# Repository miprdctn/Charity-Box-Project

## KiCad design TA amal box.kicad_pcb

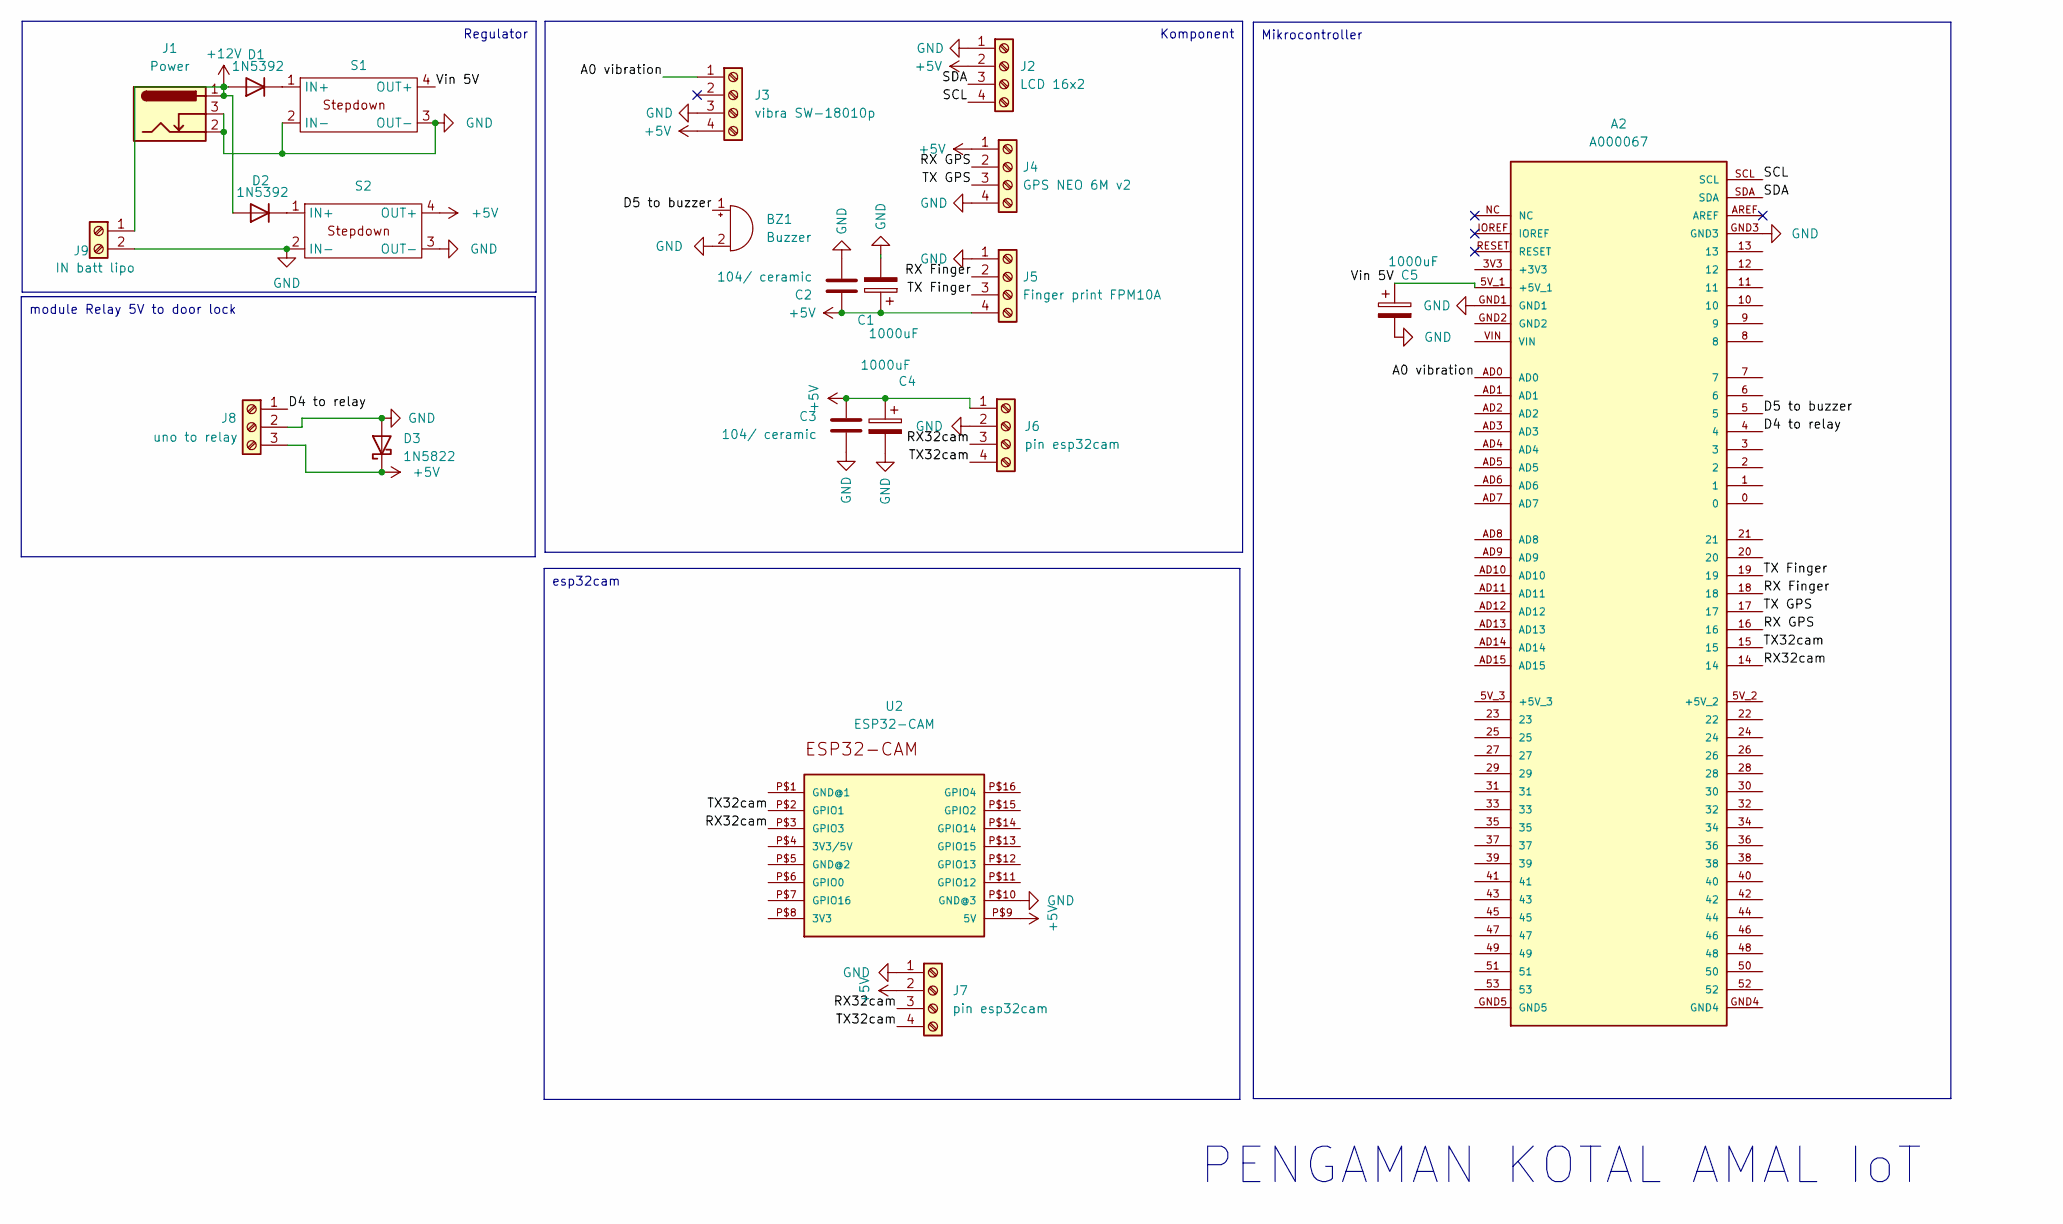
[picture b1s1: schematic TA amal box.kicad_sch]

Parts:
A2: A000067; ARDUINO_A000067
BZ1: Buzzer; JST_XH_B2B-XH-A_1x02_P2.50mm_Vertical
C1, C4, C5: 1000uF; CP_Radial_D8.0mm_P3.80mm
C2, C3: 104/ ceramic; C_Disc_D5.0mm_W2.5mm_P5.00mm
D1, D2: 1N5392; D_DO-41_SOD81_P10.16mm_Horizontal
D3: 1N5822; D_DO-201AD_P15.24mm_Horizontal
J1: Power; BarrelJack_Horizontal
J2: LCD 16x2; JST_XH_B4B-XH-A_1x04_P2.50mm_Vertical
J3: vibra SW-18010p; JST_XH_B4B-XH-A_1x04_P2.50mm_Vertical
J4: GPS NEO 6M v2; JST_XH_B4B-XH-A_1x04_P2.50mm_Vertical
J5: Finger print FPM10A; JST_XH_B4B-XH-A_1x04_P2.50mm_Vertical
J6, J7: pin esp32cam; JST_XH_B4B-XH-A_1x04_P2.50mm_Vertical
J8: uno to relay; JST_XH_B3B-XH-A_1x03_P2.50mm_Vertical
J9: IN batt lipo; TerminalBlock_Phoenix_MKDS-1,5-2-5.08_1x02_P5.08mm_Horizont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
S1, S2: YAAJ_DCDC_StepDown_LM2596
U2: ESP32-CAM

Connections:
+5V: C1.1, C2.1, C3.1, C4.1, D3.1 (K), J2.2, J3.4, J4.1, J5.4, J6.1, J7.2, J8.3, S2.4 (OUT+), U2.P$9 (5V)
+12V: D1.2 (A), D2.2 (A), J1.1, J9.1
/A0 vibration: A2.AD0, J3.1
/D4 to relay: A2.4, J8.1
/D5 to buzzer: A2.5, BZ1.1 (-)
/RX32cam: A2.14, J6.3, J7.3, U2.P$3 (GPIO3)
/RX Finger: A2.18, J5.2
/RX GPS: A2.16, J4.2
/SCL: A2.SCL, J2.4
/SDA: A2.SDA, J2.3
/TX32cam: A2.15, J6.4, J7.4, U2.P$2 (GPIO1)
/TX Finger: A2.19, J5.3
/TX GPS: A2.17, J4.3
/Vin 5V: A2.5V_1 (+5V_1), C5.1, S1.4 (OUT+)
GND: A2.GND1, A2.GND3, BZ1.2 (+), C1.2, C2.2, C3.2, C4.2, C5.2, D3.2 (A), J1.2, J1.3, J2.1, J3.3, J4.4, J5.1, J6.2, J7.1, J8.2, J9.2, S1.2 (IN-), S1.3 (OUT-), S2.2 (IN-), S2.3 (OUT-), U2.P$10 (GND@3)
unnamed: D1.1 (K), S1.1 (IN+)
unnamed: D2.1 (K), S2.1 (IN+)

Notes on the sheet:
Regulator
Mikrocontroller
Komponent
esp32cam
module Relay 5V to door lock
PENGAMAN KOTAL AMAL IoT

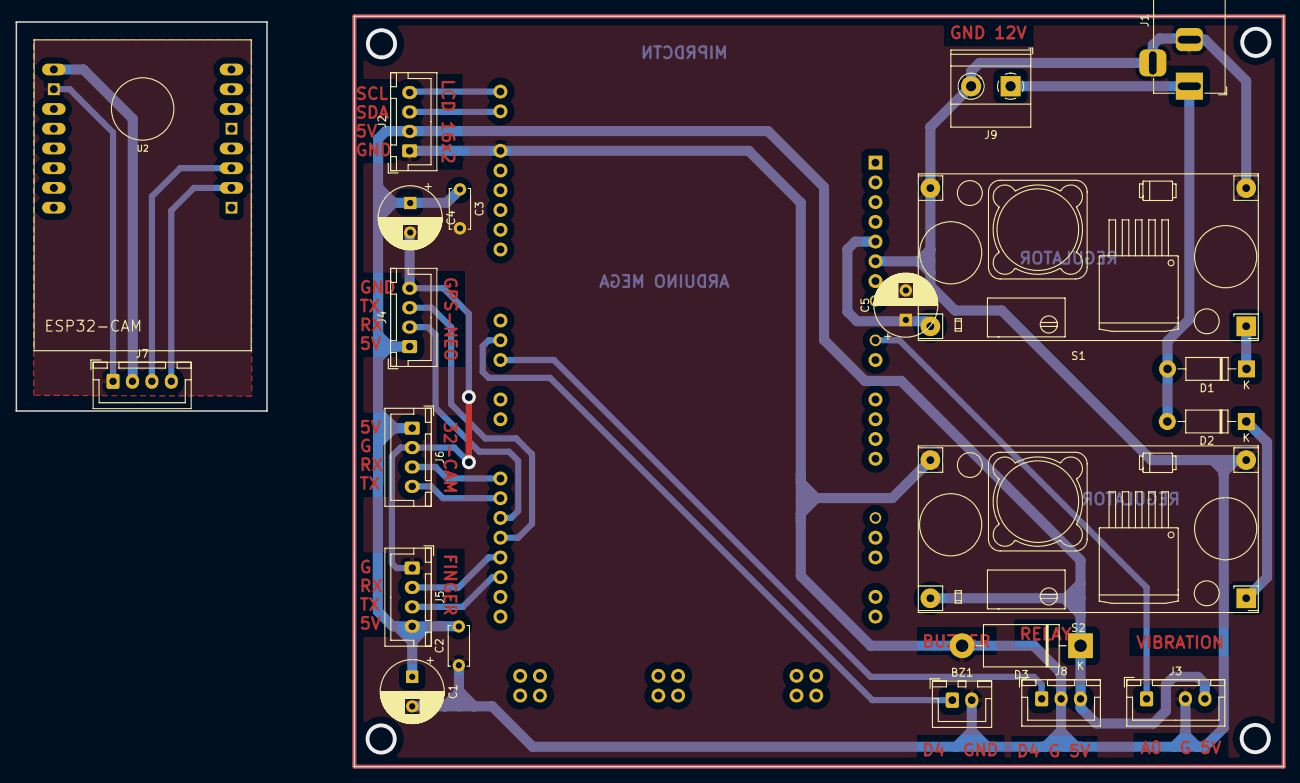
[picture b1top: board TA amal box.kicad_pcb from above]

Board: 2 copper layers, 119.6 x 96.6 mm, 22 parts (1 on the bottom side), 17 nets.

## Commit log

2025-10-13 Add files via upload
    this program for arduino
